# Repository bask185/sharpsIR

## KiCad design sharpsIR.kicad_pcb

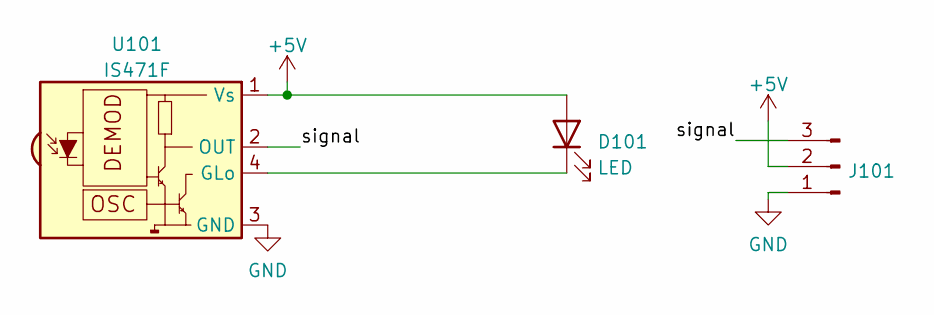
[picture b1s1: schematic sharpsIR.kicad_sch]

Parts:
D101: LED; LED_D3.0mm
J101: Conn_01x03_Male; PinHeader_1x03_P2.54mm_Horizontal
U101: IS471F; Sharp_IS471F

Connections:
+5V: D101.2 (A), J101.2, U101.1 (Vs)
/signal: J101.3, U101.2 (OUT)
GND: J101.1, U101.3 (GND)
unnamed: D101.1 (K), U101.4 (GLo)

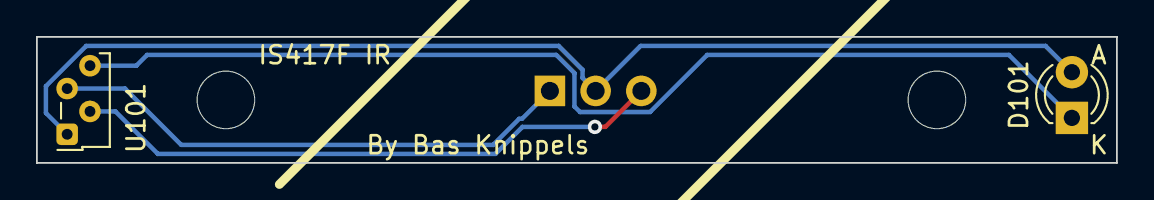
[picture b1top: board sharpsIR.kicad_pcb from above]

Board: 2 copper layers, 60.0 x 7.0 mm, 3 parts (1 on the bottom side), 4 nets.

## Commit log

2023-01-12 added gerber files
